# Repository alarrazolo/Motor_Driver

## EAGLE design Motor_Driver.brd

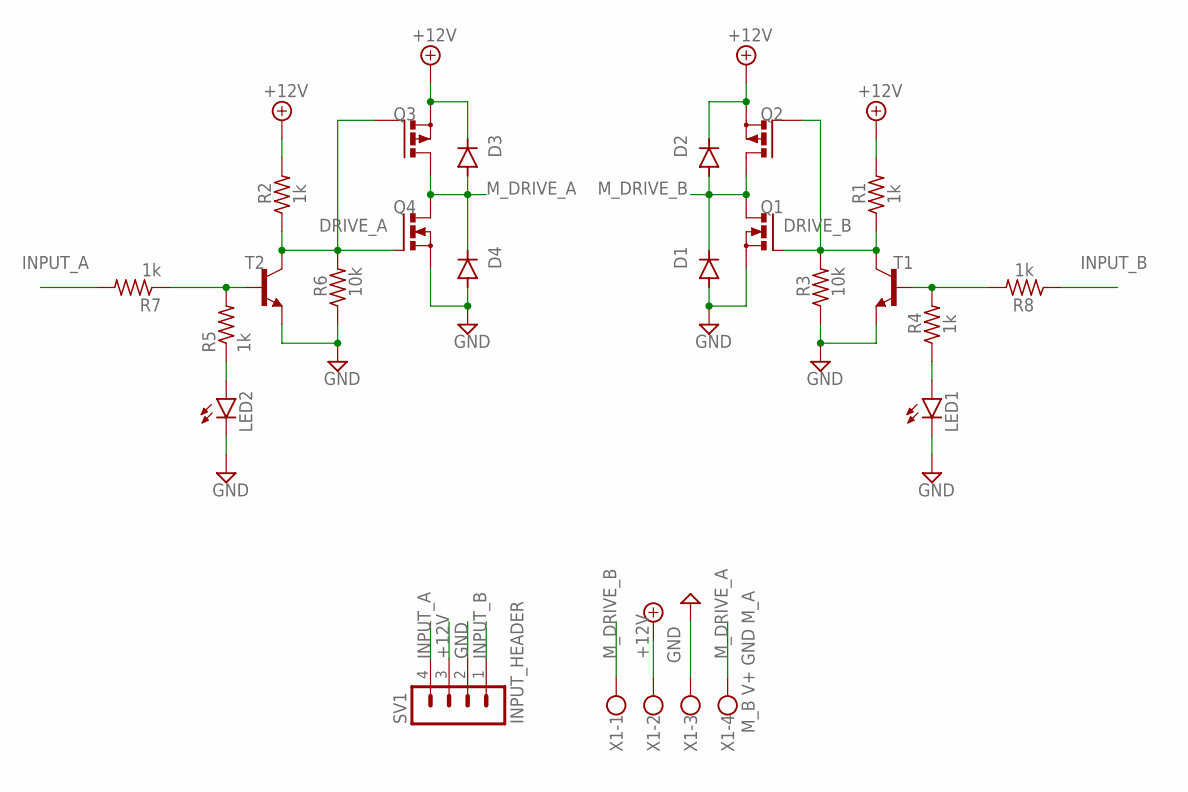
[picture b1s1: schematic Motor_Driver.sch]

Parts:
D1, D2, D3, D4: 1N4148DO35-10; DO35-10
LED1: LED_B; LED5MM
LED2: LED_A; LED5MM
Q1: N_B; TO220BV
Q2: P_B; TO220BV
Q3: P_A; TO220BV
Q4: N_A; TO220BV
R1, R2, R4, R5, R7, R8: 1k; 0207/10
R3, R6: 10k; 0207/10
SV1: INPUT_HEADER; MA04-1
T1, T2: 2N3904; TO92
X1: M_B V+ GND M_A; W237-4

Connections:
+12V: D2.C, D3.C, Q2.S, Q3.S, R1.2, R2.2, SV1.3, X1.2
DRIVE_A: Q3.G, Q4.G, R2.1, R6.2, T2.1 (C)
DRIVE_B: Q1.G, Q2.G, R1.1, R3.2, T1.1 (C)
GND: D1.A, D4.A, LED1.K (C), LED2.K (C), Q1.S, Q4.S, R3.1, R6.1, SV1.2, T1.3 (E), T2.3 (E), X1.3
INPUT_A: R7.2, SV1.4
INPUT_B: R8.1, SV1.1
M_DRIVE_A: D3.A, D4.C, Q3.D, Q4.D, X1.4
M_DRIVE_B: D1.C, D2.A, Q1.D, Q2.D, X1.1
unnamed: R5.2, R7.1, T2.2 (B)
unnamed: LED2.A, R5.1
unnamed: R4.2, R8.2, T1.2 (B)
unnamed: LED1.A, R4.1

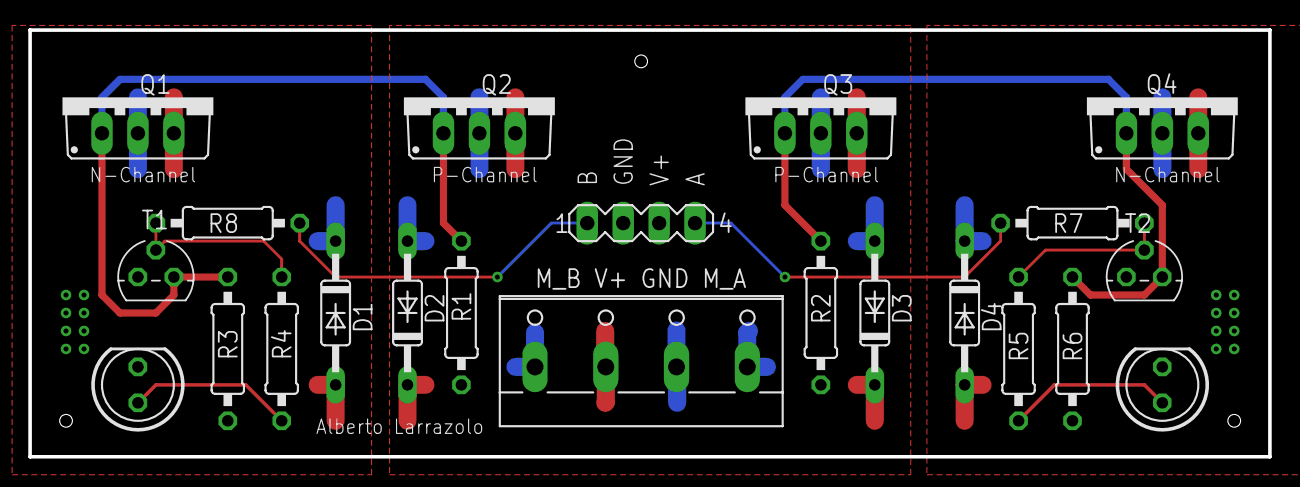
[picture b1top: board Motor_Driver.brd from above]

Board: 2 copper layers, 87.6 x 30.1 mm, 22 parts (0 on the bottom side), 12 nets.

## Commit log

2019-02-08 Increased space between MOSFETs to allow for proper heatsink size
2019-02-08 Added Fusion 360 file along with screen shot
2019-02-08 Fixed termal relif to allow higher current flow
2019-02-08 Fixed a trace that had shallow angle.
2019-02-09 Added resistors to the base of the input resistors
